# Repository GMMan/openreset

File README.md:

OpenReset Project
=================

This project is designed to allow you to easily reset your card with a
standalone device. No need to connect to a computer to use (in fact you can't
read the card from a computer using this device).

Supported cards:
- Vital Bracelet Dim
- Vital Bracelet Memory (VBM)
- TamaSma Card
- PreData Memory (for Heart Cure Watch, unreleased as of writing)

DIY hardware
------------

It is easy to build your own OpenReset from loose parts.

### Bill of materials

To build your own OpenReset, you will need the following:

- 1x Raspberry Pi Pico
- 1x microSD card breakout board (suggested model TBD)
- 1x Red LED
- 1x Resistor (for current limiting the LED; please calculate the value based
  on your LED's datasheet, but in general a 330Ω resistor will work)
- 1x Toggle switch or button if your breakout board does not have card detect
  broken out
- 1x Breadboard (optional)
- Hookup wires

### Hardware connection

1. Connect the `3V3` pin on the Pico to your positive power rail and any `GND`
   pin to your ground rail.
2. Connect the microSD card breakout to the Pico as follows:
   - Pico pin 21 to `DAT0` or `MISO`
   - Pico pin 22 to `DAT3` or `CS`
   - Pico pin 24 to `CLK` or `CLK`
   - Pico pin 25 to `CMD` or `MOSI`
   - Pico pin 26 to card detect. Note, if your breakout board does not have a
     card detect pin, you can connect a toggle switch or button to pin 26, and
     connect the other side to ground.
3. Connect the red LED such that the anode end has the Pico's pin 6 upstream.
   Connect a resistor before or after the LED, and connect the loose end of the
   LED or resistor to ground.

Carrier board
-------------

Alternatively, you can have a carrier board fabbed and solder the Pi Pico to it
along with a few other components.

Board design files are in the [carrier_board](carrier_board) directory. Gerbers
are available in the [carrier_board/gerber](carrier_board/gerber) directory,
and are available as a [ZIP file](carrier_board/gerber/openreset_carrier_board_v1c.zip).

### Bill of materials

- 1x Raspberry Pi Pico (`U1`) ([Official resellers](https://www.raspberrypi.com/products/raspberry-pi-pico/#find-reseller))
- 1x Molex 0475710001 push-pull microSD card connector (`J1`) ([Digikey](https://www.digikey.ca/en/products/detail/molex/0475710001/3262277))
- 1x 0603 Red LED (`D1`)
- 1x 0603 Resistor (`R1`) (for current limiting the LED; please calculate the
  value based on your LED's datasheet, but in general a 330Ω resistor will work)

Software setup
--------------

1. Install MicroPython on to your Pi Pico
   - Download a recent build from [here](https://micropython.org/download/rp2-pico/)
   - Hold the `BOOTSEL` button on your Pico, then plug the Pico into your
     computer while still holding the button. You can release the button
     once the Pico shows up on your computer as a USB drive.
   - Drag the .uf2 firmware you have downloaded to the USB drive, and the
     Pico will install the firmware and reboot
2. Upload the code in the [firmware](firmware) directory to the Pico
   - I use [Thonny](https://thonny.org/). After you install it, open it up
     and click the button at the bottom right of the screen. Select
     `MicroPython (Raspberry Pi Pico)`.
   - Open up each file in the firmware directory, and select `File ->
     Save copy...` from the menu strip. Click `Raspbery Pi Pico` when asked
     where to save to. Type in the name of the file in the `File name` box,
     and click `OK`.
3. Replug the Pico and verify the code is installed
   - The red LED should be lit

Usage
-----

The board is easy to use. All you have to do is insert your card and the device
will automatically perform the erase. The red LED will always be on to indicate
power, and the green LED on the Pi Pico will light up when the erase is in
progress. After the erase is completed, the green LED will extinguish. If there
is an error, the red LED will blink off a number of times to indicate the error.

- 1 time: wrong card type, check you are using the correct card
- 2 times: wrong flash chip; if you are sure your card is genuine, file an
  issue in this repo
- 3 times: card is not responding as expected

There are messages printed to UART if you need more info on troubleshooting.
I suggest loading the code up in Thonny and checking the shell for the
messages.

**Warning:** TamaSma Card locking area is embedded in the card header. By
nature of SPI NOR flash, changing this data will involve erasing the sector,
so there is a risk of breaking the data if the connection is bad. Therefore,
be careful when plugging in a TamaSma Card to plug it in firmly.

If your are using a DIY build and your microSD breakout board does not have a
card detect pin, then you can use the switch/button alternative. Flip the
switch or hold the button after you have inserted a card. The process will
complete and the red LED will flash if there are errors. If you are using a
button, make sure to hold the button until the error has finished blinking, if
applicable. Flip the switch again or release the button before inserting the
next card.

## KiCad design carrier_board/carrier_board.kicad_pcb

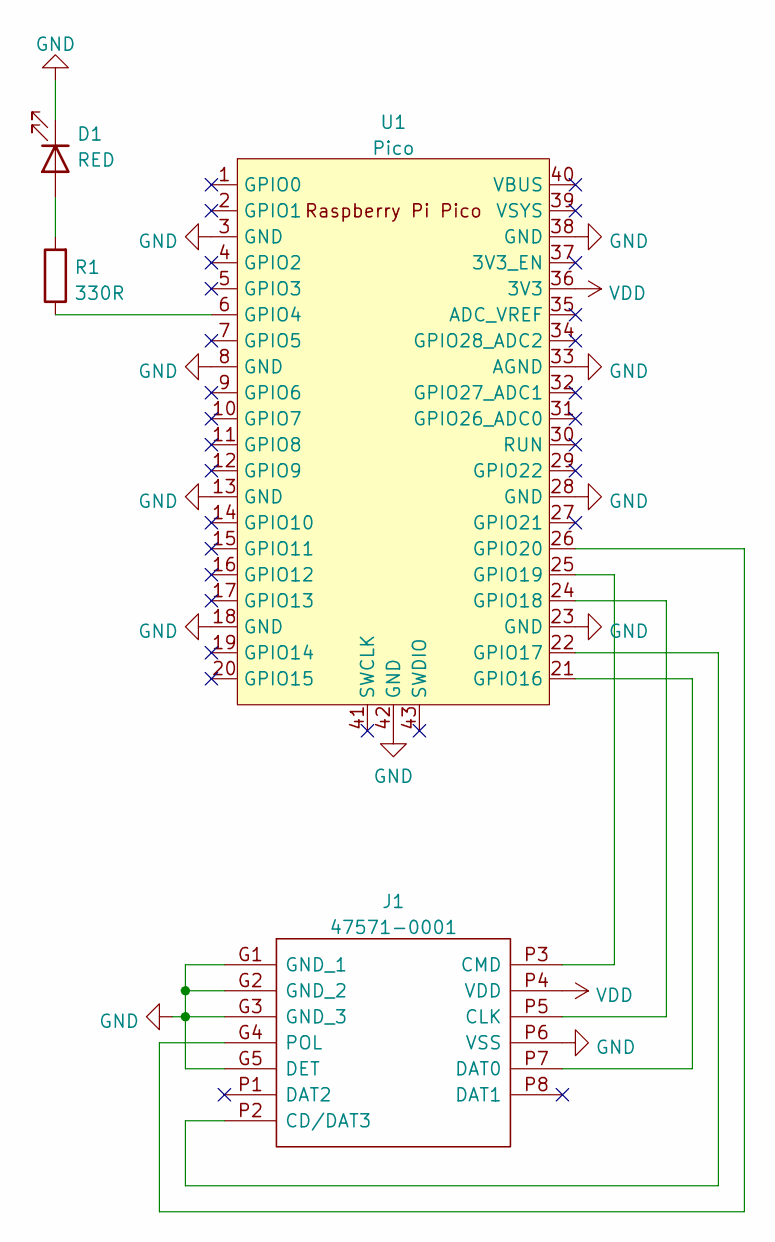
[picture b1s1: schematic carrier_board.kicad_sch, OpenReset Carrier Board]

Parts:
D1: RED; LED_0603_1608Metric_Pad1.05x0.95mm_HandSolder
J1: 47571-0001; 475710001; Mouser Part Number 538-47571-0001
R1: 330R; R_0603_1608Metric_Pad0.98x0.95mm_HandSolder
U1: Pico; RPi_Pico_SMD_TH

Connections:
GND: D1.1 (K), J1.G1 (GND_1), J1.G2 (GND_2), J1.G3 (GND_3), J1.G5 (DET), J1.P6 (VSS), U1.3 (GND), U1.8 (GND), U1.13 (GND), U1.18 (GND), U1.23 (GND), U1.28 (GND), U1.33 (AGND), U1.38 (GND), U1.42 (GND)
unnamed: J1.G4 (POL), U1.26 (GPIO20)
unnamed: J1.P2 (CD/DAT3), U1.22 (GPIO17)
unnamed: J1.P3 (CMD), U1.25 (GPIO19)
unnamed: J1.P5 (CLK), U1.24 (GPIO18)
unnamed: J1.P7 (DAT0), U1.21 (GPIO16)
unnamed: D1.2 (A), R1.2
unnamed: R1.1, U1.6 (GPIO4)
VDD: J1.P4 (VDD), U1.36 (3V3)

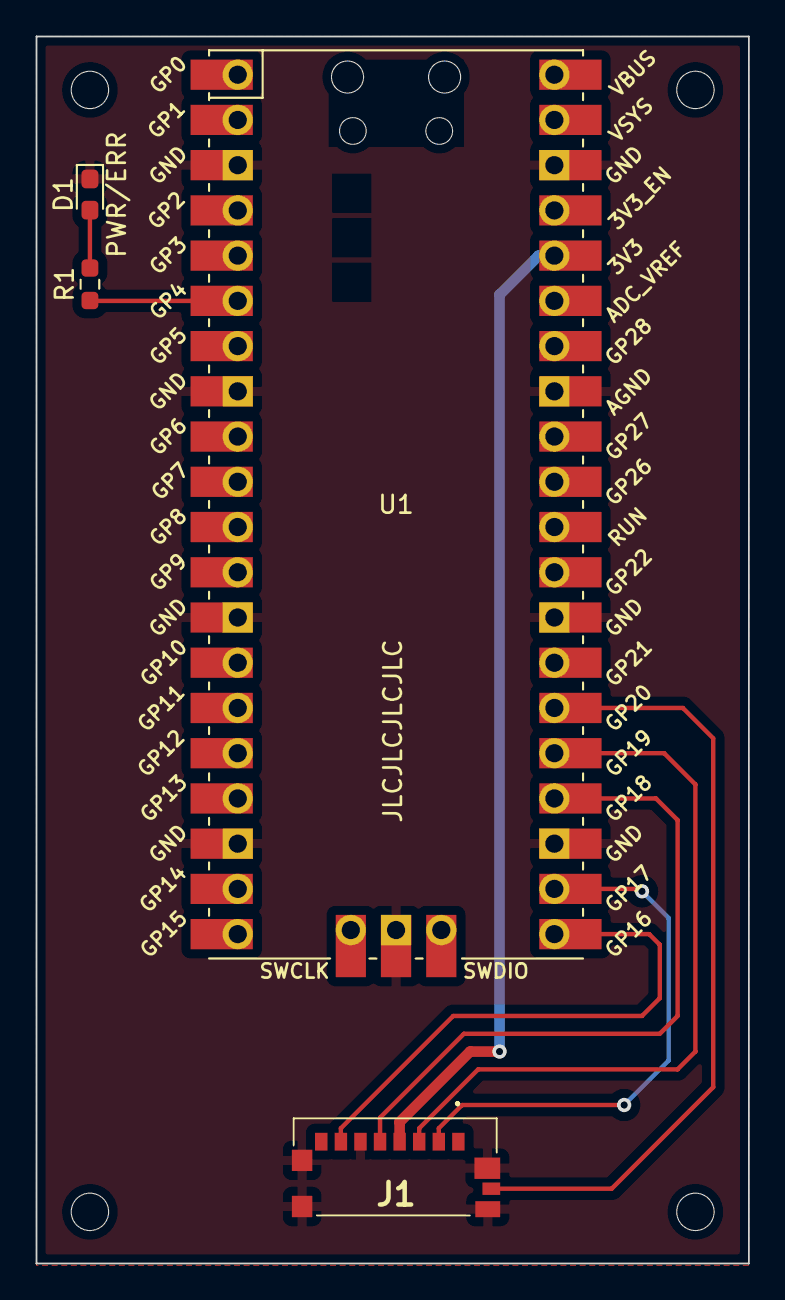
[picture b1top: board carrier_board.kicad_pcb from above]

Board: 2 copper layers, 40.0 x 68.9 mm, 4 parts (0 on the bottom side), 9 nets.

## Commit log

2022-03-20 Change red LED from GP2 to GP4 to free up UART RX
    Also add label to LED on board
2022-03-21 Fix weird 3v3 routing
2022-04-10 Thicken power trace
2022-04-10 Update zip path in readme
2022-04-10 Update LED connection instruction
2022-04-11 Change firmware to patcher mode
2022-04-11 Set read buffer for sector to None so it can be garbage collected
2022-06-18 Refactor and add support for TamaSma Card and PreData Memory
2022-09-15 Update PreData Memory resetter with new info
2022-09-15 Remove sector erase for PreData Memory
    You don't need to erase when you're just turning everything to zeroes
